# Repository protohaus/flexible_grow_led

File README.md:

# Flexible Grow LED

This project is the result of Sören Krusche's student research project.
The aim was to create a flexible LED light for growing plants with adjustable wavelengths.
It encompases the CAD files for the electronics and 3D printed components as well as the source code for the ESP8266 and the Node-RED flow.

## Node-RED Dashboard

The flow can be found in the Node-RED_Flow folder.

## PCB Design

Insert PCB image

The design files can be found in the CAD/EAGLE folder.

## 3D Printed Model

Insert 3D printed model

The design files can be found in the CAD/Fusion360 folder.

## PlatformIO Project

The source code for the ESP8266 can be found in the PlatformIO folder.

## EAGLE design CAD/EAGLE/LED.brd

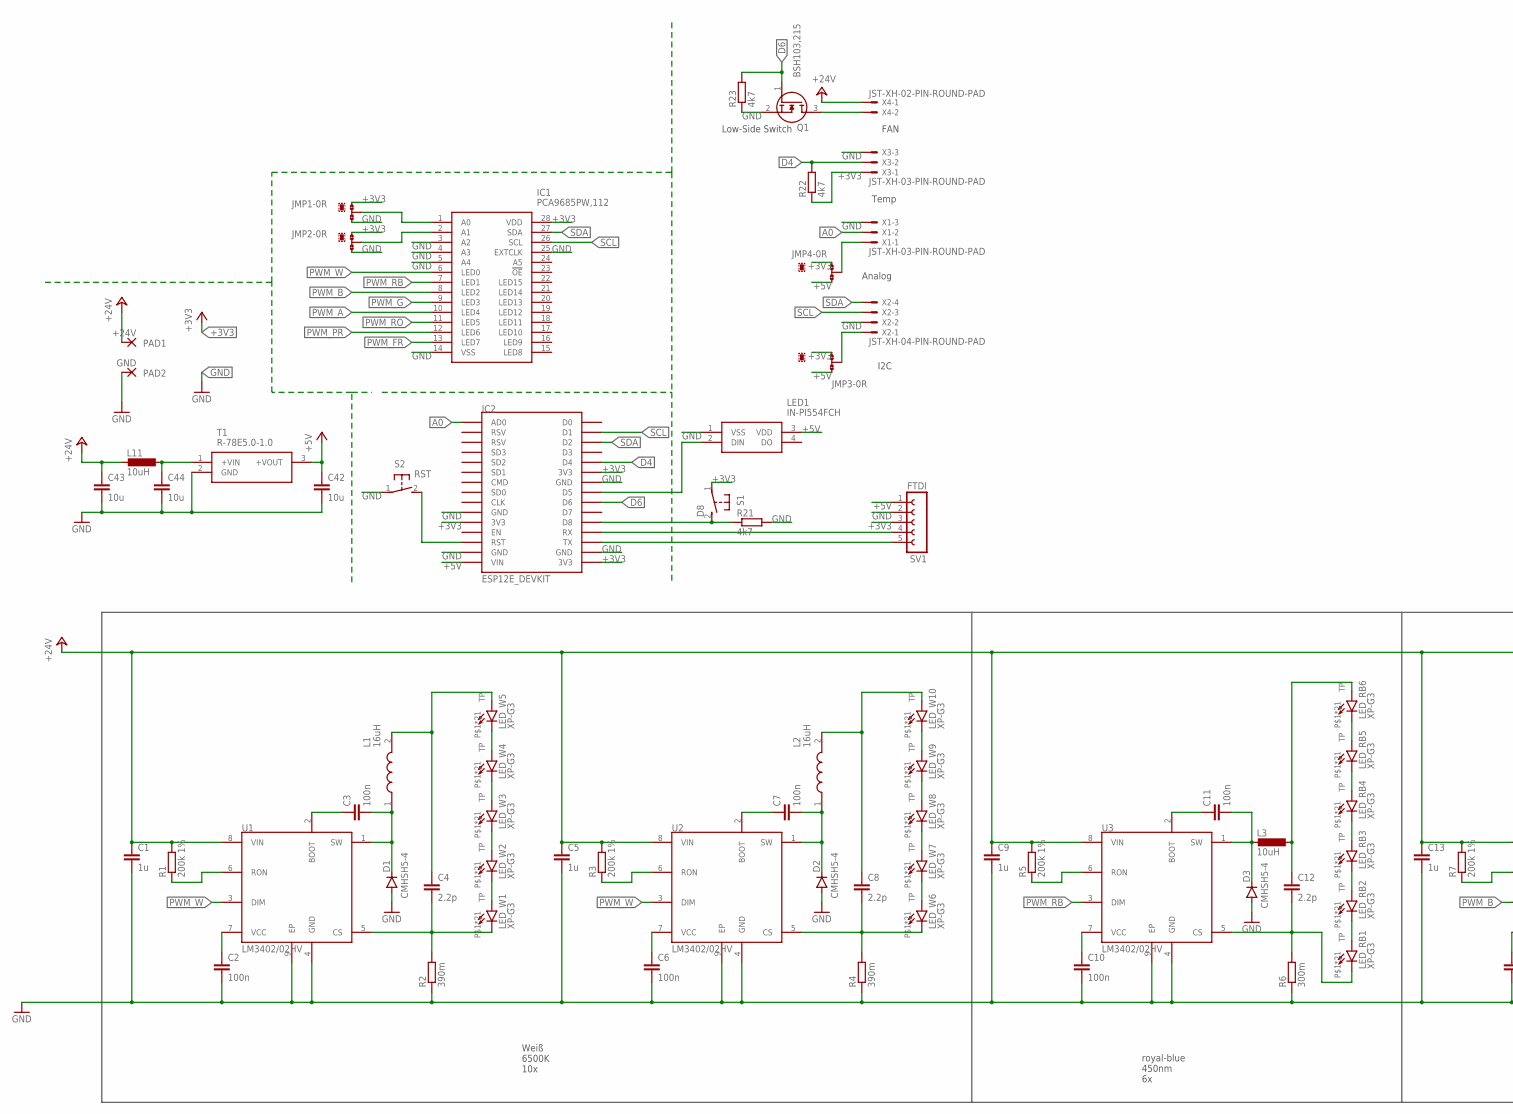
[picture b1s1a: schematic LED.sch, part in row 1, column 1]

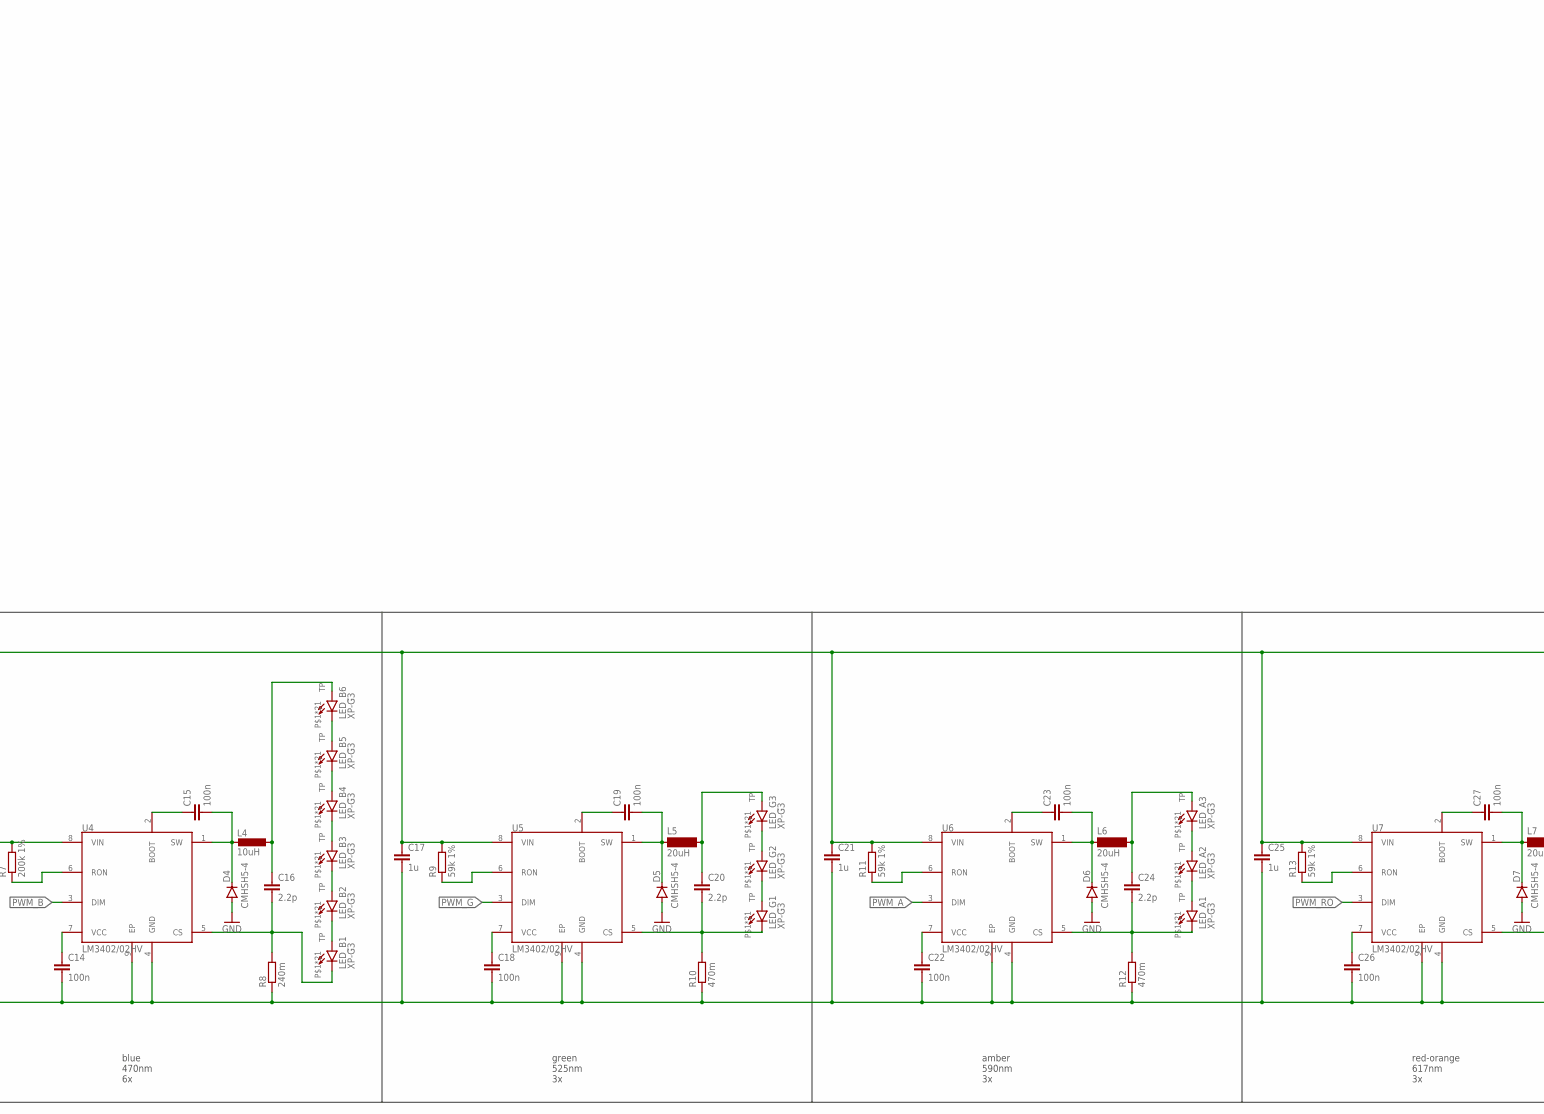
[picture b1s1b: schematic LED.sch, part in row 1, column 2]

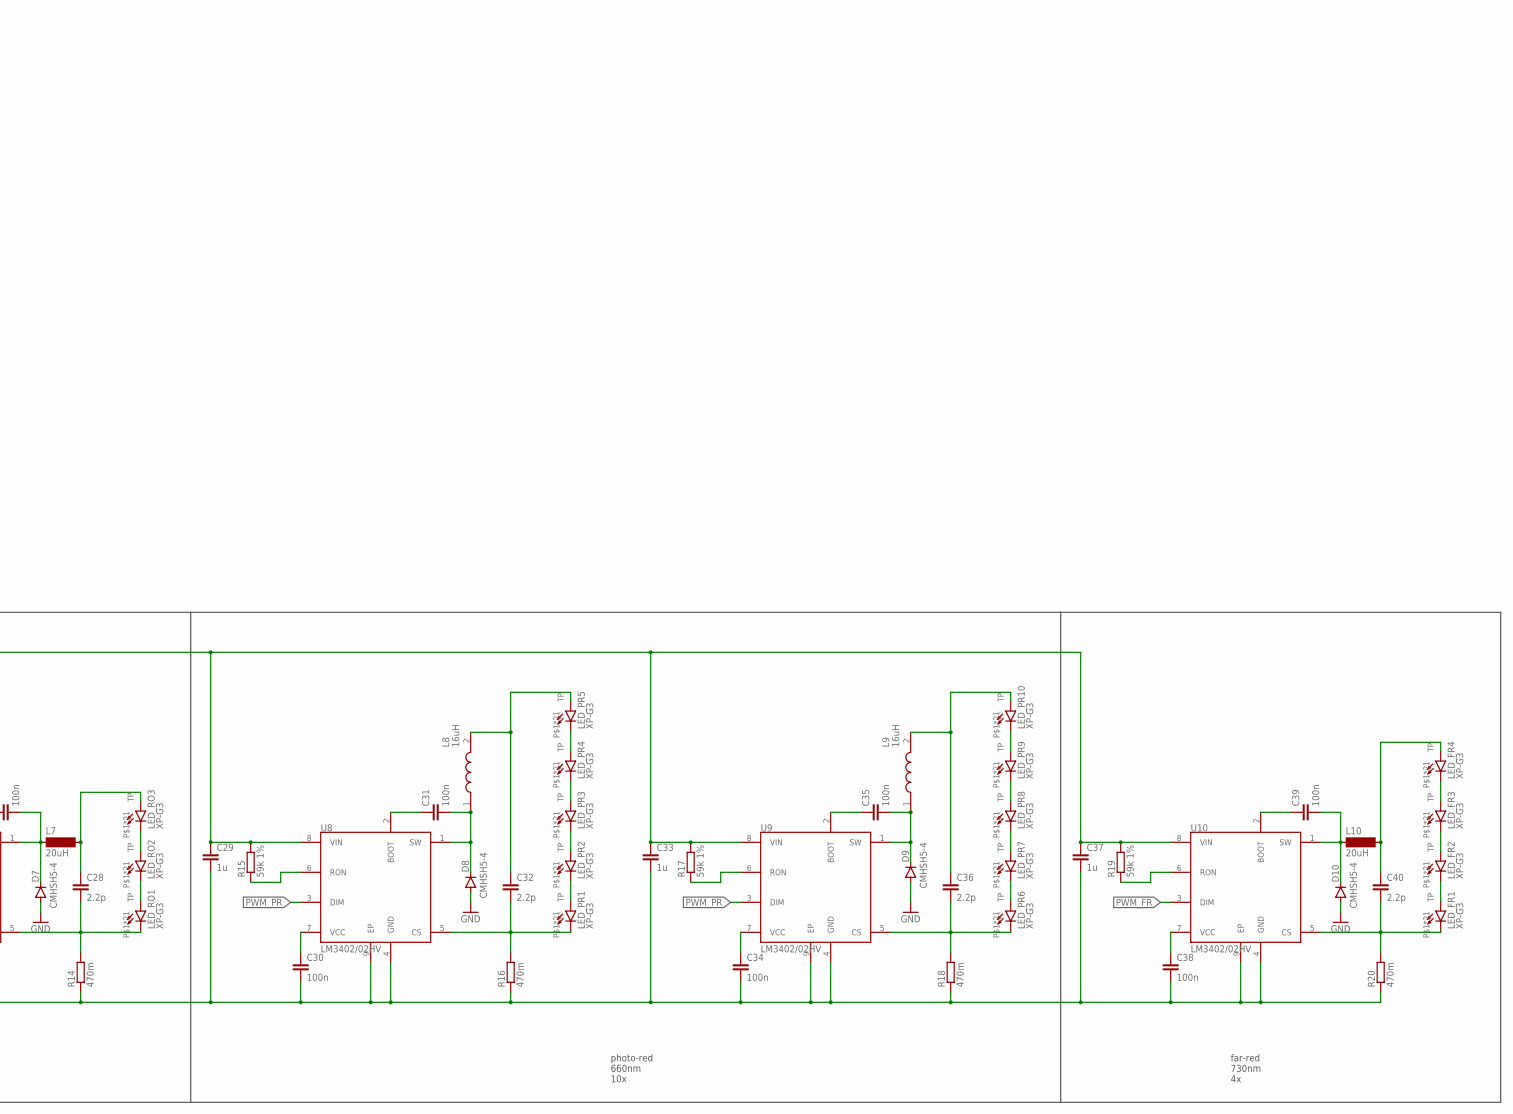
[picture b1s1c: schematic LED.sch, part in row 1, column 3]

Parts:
C1, C5, C9, C13, C17, C21, C25, C29, C33, C37: 1u; C1206
C2, C3, C6, C7, C10, C11, C14, C15, C18, C19, C22, C23, C26, C27, C30, C31, C34, C35, C38, C39: 100n; C0805
C4, C8, C12, C16, C20, C24, C28, C32, C36, C40: 2.2p; C1206
C42, C43, C44: 10u; C1210
D1, D2, D3, D4, D5, D6, D7, D8, D9, D10: CMHSH5-4; SOD123
IC1: PCA9685PW,112; SOP65P640X110-28N
IC2: ESP12E_DEVKIT
JMP1, JMP2, JMP3, JMP4: 0R-JUMPA; A0R-JMP
L1, L2, L8, L9: 16uH; INDPM101101X680N
L3, L4, L11: 10uH; L3225M
L5, L6, L7, L10: 20uH; PF0382.223NLT
LED1: IN-PI554FCH; INPI554FCH
LED_A1, LED_A2, LED_A3: XP-G3; CREE_XLAMP
LED_B1, LED_B2, LED_B3, LED_B4, LED_B5, LED_B6: XP-G3; CREE_XLAMP
LED_FR1, LED_FR2, LED_FR3, LED_FR4: XP-G3; CREE_XLAMP
LED_G1, LED_G2, LED_G3: XP-G3; CREE_XLAMP
LED_PR1, LED_PR2, LED_PR3, LED_PR4, LED_PR5, LED_PR6, LED_PR7, LED_PR8, LED_PR9, LED_PR10: XP-G3; CREE_XLAMP
LED_RB1, LED_RB2, LED_RB3, LED_RB4, LED_RB5, LED_RB6: XP-G3; CREE_XLAMP
LED_RO1, LED_RO2, LED_RO3: XP-G3; CREE_XLAMP
LED_W1, LED_W2, LED_W3, LED_W4, LED_W5, LED_W6, LED_W7, LED_W8, LED_W9, LED_W10: XP-G3; CREE_XLAMP
PAD1: +24V; 3,81/1,4
PAD2: GND; 3,81/1,4
Q1: BSH103,215; SOT95P230X110-3N
R1, R3, R5, R7: 200k 1%; R0805
R2, R4: 390m; R0805
R6: 300m; R0805
R8: 240m; R0805
R9, R11, R13, R15, R17, R19: 59k 1%; R0805
R10, R12, R14, R16, R18, R20: 470m; R0805
R21, R22, R23: 4k7; R0805
S1: D8; B3F-31XX
S2: RST; B3F-31XX
SV1: FTDI; FE05-1
T1: R-78E5.0-1.0
U1, U2, U3, U4, U5, U6, U7, U8, U9, U10: LM3402/02HV; SOIC127P600X170-9T228N
X1, X3: JST-XH-03-PIN-ROUND-PAD; JST-XH-03-PACKAGE-ROUND-PAD
X2: JST-XH-04-PIN-ROUND-PAD; JST-XH-04-PACKAGE-ROUND-PAD
X4: JST-XH-02-PIN-ROUND-PAD; JST-XH-02-PACKAGE-ROUND-PAD

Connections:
+3V3: IC1.28 (VDD), IC2.3V3@0 (3V3), IC2.3V3@1 (3V3), IC2.3V3@2 (3V3), JMP1.1, JMP2.1, JMP3.1, JMP4.1, R22.1, S1.1, SV1.3, X3.1
+5V: C42.1, IC2.VIN, JMP3.3, JMP4.3, LED1.3 (VDD), SV1.1, T1.3 (+VOUT)
+24V: C1.1, C5.1, C9.1, C13.1, C17.1, C21.1, C25.1, C29.1, C33.1, C37.1, C43.1, L11.2, PAD1.1, R1.2, R3.2, R5.2, R7.2, R9.2, R11.2, R13.2, R15.2, R17.2, R19.2, U1.8 (VIN), U2.8 (VIN), U3.8 (VIN), U4.8 (VIN), U5.8 (VIN), U6.8 (VIN), U7.8 (VIN), U8.8 (VIN), U9.8 (VIN), U10.8 (VIN), X4.1
A0: IC2.AD0, X1.2
D4: IC2.D4, R22.2, X3.2
D6: IC2.D6, Q1.1 (G), R23.2
GND: C1.2, C2.2, C5.2, C6.2, C9.2, C10.2, C13.2, C14.2, C17.2, C18.2, C21.2, C22.2, C25.2, C26.2, C29.2, C30.2, C33.2, C34.2, C37.2, C38.2, C42.2, C43.2, C44.2, D1.A, D2.A, D3.A, D4.A, D5.A, D6.A, D7.A, D8.A, D9.A, D10.A, IC1.3 (A2), IC1.4 (A3), IC1.5 (A4), IC1.14 (VSS), IC1.25 (EXTCLK), IC2.GND@0 (GND), IC2.GND@1 (GND), IC2.GND@2 (GND), IC2.GND@3 (GND), JMP1.3, JMP2.3, LED1.1 (VSS), PAD2.1, Q1.2 (S), R2.1, R4.1, R6.1, R8.1, R10.1, R12.1, R14.1, R16.1, R18.1, R20.1, R21.2, R23.1, S2.1, SV1.2, T1.2 (GND), U1.4 (GND), U1.9 (EP), U2.4 (GND), U2.9 (EP), U3.4 (GND), U3.9 (EP), U4.4 (GND), U4.9 (EP), U5.4 (GND), U5.9 (EP), U6.4 (GND), U6.9 (EP), U7.4 (GND), U7.9 (EP), U8.4 (GND), U8.9 (EP), U9.4 (GND), U9.9 (EP), U10.4 (GND), U10.9 (EP), X1.3, X2.2, X3.3
unnamed: LED_W6.A, LED_W6.A@1 (A), LED_W7.C, LED_W7.C@1 (C)
unnamed: LED_W7.A, LED_W7.A@1 (A), LED_W8.C, LED_W8.C@1 (C)
unnamed: LED_W8.A, LED_W8.A@1 (A), LED_W9.C, LED_W9.C@1 (C)
unnamed: LED_W9.A, LED_W9.A@1 (A), LED_W10.C, LED_W10.C@1 (C)
unnamed: R3.1, U2.6 (RON)
unnamed: R1.1, U1.6 (RON)
unnamed: C3.1, U1.2 (BOOT)
unnamed: C3.2, D1.C, L1.1, U1.1 (SW)
unnamed: C2.1, U1.7 (VCC)
unnamed: LED_W1.A, LED_W1.A@1 (A), LED_W2.C, LED_W2.C@1 (C)
unnamed: LED_W2.A, LED_W2.A@1 (A), LED_W3.C, LED_W3.C@1 (C)
unnamed: LED_W3.A, LED_W3.A@1 (A), LED_W4.C, LED_W4.C@1 (C)
unnamed: LED_W4.A, LED_W4.A@1 (A), LED_W5.C, LED_W5.C@1 (C)
unnamed: LED_RB5.A, LED_RB5.A@1 (A), LED_RB6.C, LED_RB6.C@1 (C)
unnamed: C4.2, LED_W1.C, LED_W1.C@1 (C), R2.2, U1.5 (CS)
unnamed: C7.1, U2.2 (BOOT)
unnamed: C7.2, D2.C, L2.1, U2.1 (SW)
unnamed: C6.1, U2.7 (VCC)
unnamed: LED_B1.A, LED_B1.A@1 (A), LED_B2.C, LED_B2.C@1 (C)
unnamed: C8.1, L2.2, LED_W10.A, LED_W10.A@1 (A)
unnamed: LED_B2.A, LED_B2.A@1 (A), LED_B3.C, LED_B3.C@1 (C)
unnamed: LED_B3.A, LED_B3.A@1 (A), LED_B4.C, LED_B4.C@1 (C)
unnamed: LED_B4.A, LED_B4.A@1 (A), LED_B5.C, LED_B5.C@1 (C)
unnamed: LED_B5.A, LED_B5.A@1 (A), LED_B6.C, LED_B6.C@1 (C)
unnamed: IC1.1 (A0), JMP1.2
unnamed: IC2.D8, R21.1, S1.2 (S)
unnamed: C8.2, LED_W6.C, LED_W6.C@1 (C), R4.2, U2.5 (CS)
unnamed: LED_RB1.A, LED_RB1.A@1 (A), LED_RB2.C, LED_RB2.C@1 (C)
unnamed: LED_RB2.A, LED_RB2.A@1 (A), LED_RB3.C, LED_RB3.C@1 (C)
unnamed: LED_RB3.A, LED_RB3.A@1 (A), LED_RB4.C, LED_RB4.C@1 (C)
unnamed: LED_RB4.A, LED_RB4.A@1 (A), LED_RB5.C, LED_RB5.C@1 (C)
unnamed: R5.1, U3.6 (RON)
unnamed: C11.1, U3.2 (BOOT)
unnamed: C11.2, D3.C, L3.2, U3.1 (SW)
unnamed: C10.1, U3.7 (VCC)
unnamed: C12.1, L3.1, LED_RB6.A, LED_RB6.A@1 (A)
unnamed: C12.2, LED_RB1.C, LED_RB1.C@1 (C), R6.2, U3.5 (CS)
unnamed: C44.1, L11.1, T1.1 (+VIN)
unnamed: IC1.2 (A1), JMP2.2
unnamed: JMP3.2, X2.1
unnamed: IC2.RST, S2.2 (S)
unnamed: JMP4.2, X1.1
unnamed: IC2.D5, LED1.2 (DIN)
unnamed: IC2.RX, SV1.4
unnamed: IC2.TX, SV1.5
unnamed: Q1.3 (D), X4.2
unnamed: R7.1, U4.6 (RON)
unnamed: C15.1, U4.2 (BOOT)
unnamed: C15.2, D4.C, L4.2, U4.1 (SW)
unnamed: C14.1, U4.7 (VCC)
unnamed: C16.1, L4.1, LED_B6.A, LED_B6.A@1 (A)
unnamed: C16.2, LED_B1.C, LED_B1.C@1 (C), R8.2, U4.5 (CS)
unnamed: LED_G1.A, LED_G1.A@1 (A), LED_G2.C, LED_G2.C@1 (C)
unnamed: LED_G2.A, LED_G2.A@1 (A), LED_G3.C, LED_G3.C@1 (C)
unnamed: R9.1, U5.6 (RON)
unnamed: C19.1, U5.2 (BOOT)
unnamed: C19.2, D5.C, L5.P0, U5.1 (SW)
unnamed: C18.1, U5.7 (VCC)
unnamed: C20.1, L5.P1, LED_G3.A, LED_G3.A@1 (A)
unnamed: C20.2, LED_G1.C, LED_G1.C@1 (C), R10.2, U5.5 (CS)
unnamed: LED_A1.A, LED_A1.A@1 (A), LED_A2.C, LED_A2.C@1 (C)
unnamed: LED_A2.A, LED_A2.A@1 (A), LED_A3.C, LED_A3.C@1 (C)
unnamed: R11.1, U6.6 (RON)
unnamed: C23.1, U6.2 (BOOT)
unnamed: C23.2, D6.C, L6.P0, U6.1 (SW)
unnamed: C22.1, U6.7 (VCC)
unnamed: C24.1, L6.P1, LED_A3.A, LED_A3.A@1 (A)
unnamed: C24.2, LED_A1.C, LED_A1.C@1 (C), R12.2, U6.5 (CS)
unnamed: LED_RO1.A, LED_RO1.A@1 (A), LED_RO2.C, LED_RO2.C@1 (C)
unnamed: LED_RO2.A, LED_RO2.A@1 (A), LED_RO3.C, LED_RO3.C@1 (C)
unnamed: R13.1, U7.6 (RON)
unnamed: C27.1, U7.2 (BOOT)
unnamed: C27.2, D7.C, L7.P0, U7.1 (SW)
unnamed: C26.1, U7.7 (VCC)
unnamed: C28.1, L7.P1, LED_RO3.A, LED_RO3.A@1 (A)
unnamed: C28.2, LED_RO1.C, LED_RO1.C@1 (C), R14.2, U7.5 (CS)
unnamed: LED_PR1.A, LED_PR1.A@1 (A), LED_PR2.C, LED_PR2.C@1 (C)
unnamed: LED_PR2.A, LED_PR2.A@1 (A), LED_PR3.C, LED_PR3.C@1 (C)
unnamed: LED_PR3.A, LED_PR3.A@1 (A), LED_PR4.C, LED_PR4.C@1 (C)
unnamed: LED_PR4.A, LED_PR4.A@1 (A), LED_PR5.C, LED_PR5.C@1 (C)
unnamed: R15.1, U8.6 (RON)
unnamed: C31.1, U8.2 (BOOT)
unnamed: C31.2, D8.C, L8.1, U8.1 (SW)
unnamed: C30.1, U8.7 (VCC)
unnamed: C32.1, L8.2, LED_PR5.A, LED_PR5.A@1 (A)
unnamed: C32.2, LED_PR1.C, LED_PR1.C@1 (C), R16.2, U8.5 (CS)
unnamed: LED_PR6.A, LED_PR6.A@1 (A), LED_PR7.C, LED_PR7.C@1 (C)
unnamed: LED_PR7.A, LED_PR7.A@1 (A), LED_PR8.C, LED_PR8.C@1 (C)
unnamed: LED_PR8.A, LED_PR8.A@1 (A), LED_PR9.C, LED_PR9.C@1 (C)
unnamed: LED_PR9.A, LED_PR9.A@1 (A), LED_PR10.C, LED_PR10.C@1 (C)
unnamed: R17.1, U9.6 (RON)
unnamed: C35.1, U9.2 (BOOT)
unnamed: C35.2, D9.C, L9.1, U9.1 (SW)
unnamed: C34.1, U9.7 (VCC)
unnamed: C36.1, L9.2, LED_PR10.A, LED_PR10.A@1 (A)
unnamed: C36.2, LED_PR6.C, LED_PR6.C@1 (C), R18.2, U9.5 (CS)
unnamed: LED_FR1.A, LED_FR1.A@1 (A), LED_FR2.C, LED_FR2.C@1 (C)
unnamed: LED_FR2.A, LED_FR2.A@1 (A), LED_FR3.C, LED_FR3.C@1 (C)
unnamed: LED_FR3.A, LED_FR3.A@1 (A), LED_FR4.C, LED_FR4.C@1 (C)
unnamed: R19.1, U10.6 (RON)
unnamed: C39.1, U10.2 (BOOT)
unnamed: C39.2, D10.C, L10.P0, U10.1 (SW)
unnamed: C38.1, U10.7 (VCC)
unnamed: C40.1, L10.P1, LED_FR4.A, LED_FR4.A@1 (A)
unnamed: C40.2, LED_FR1.C, LED_FR1.C@1 (C), R20.2, U10.5 (CS)
unnamed: C4.1, L1.2, LED_W5.A, LED_W5.A@1 (A)
PWM_A: IC1.10 (LED4), U6.3 (DIM)
PWM_B: IC1.8 (LED2), U4.3 (DIM)
PWM_FR: IC1.13 (LED7), U10.3 (DIM)
PWM_G: IC1.9 (LED3), U5.3 (DIM)
PWM_PR: IC1.12 (LED6), U8.3 (DIM), U9.3 (DIM)
PWM_RB: IC1.7 (LED1), U3.3 (DIM)
PWM_RO: IC1.11 (LED5), U7.3 (DIM)
PWM_W: IC1.6 (LED0), U1.3 (DIM), U2.3 (DIM)
SCL: IC1.26 (SCL), IC2.D1, X2.3
SDA: IC1.27 (SDA), IC2.D2, X2.4

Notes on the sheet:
Weiß 6500K 10x
royal-blue 450nm 6x
blue 470nm 6x
green 525nm 3x
amber 590nm 3x
red-orange 617nm 3x
photo-red 660nm 10x
far-red 730nm 4x
I2C
Analog
Temp
FAN
Low-Side Switch

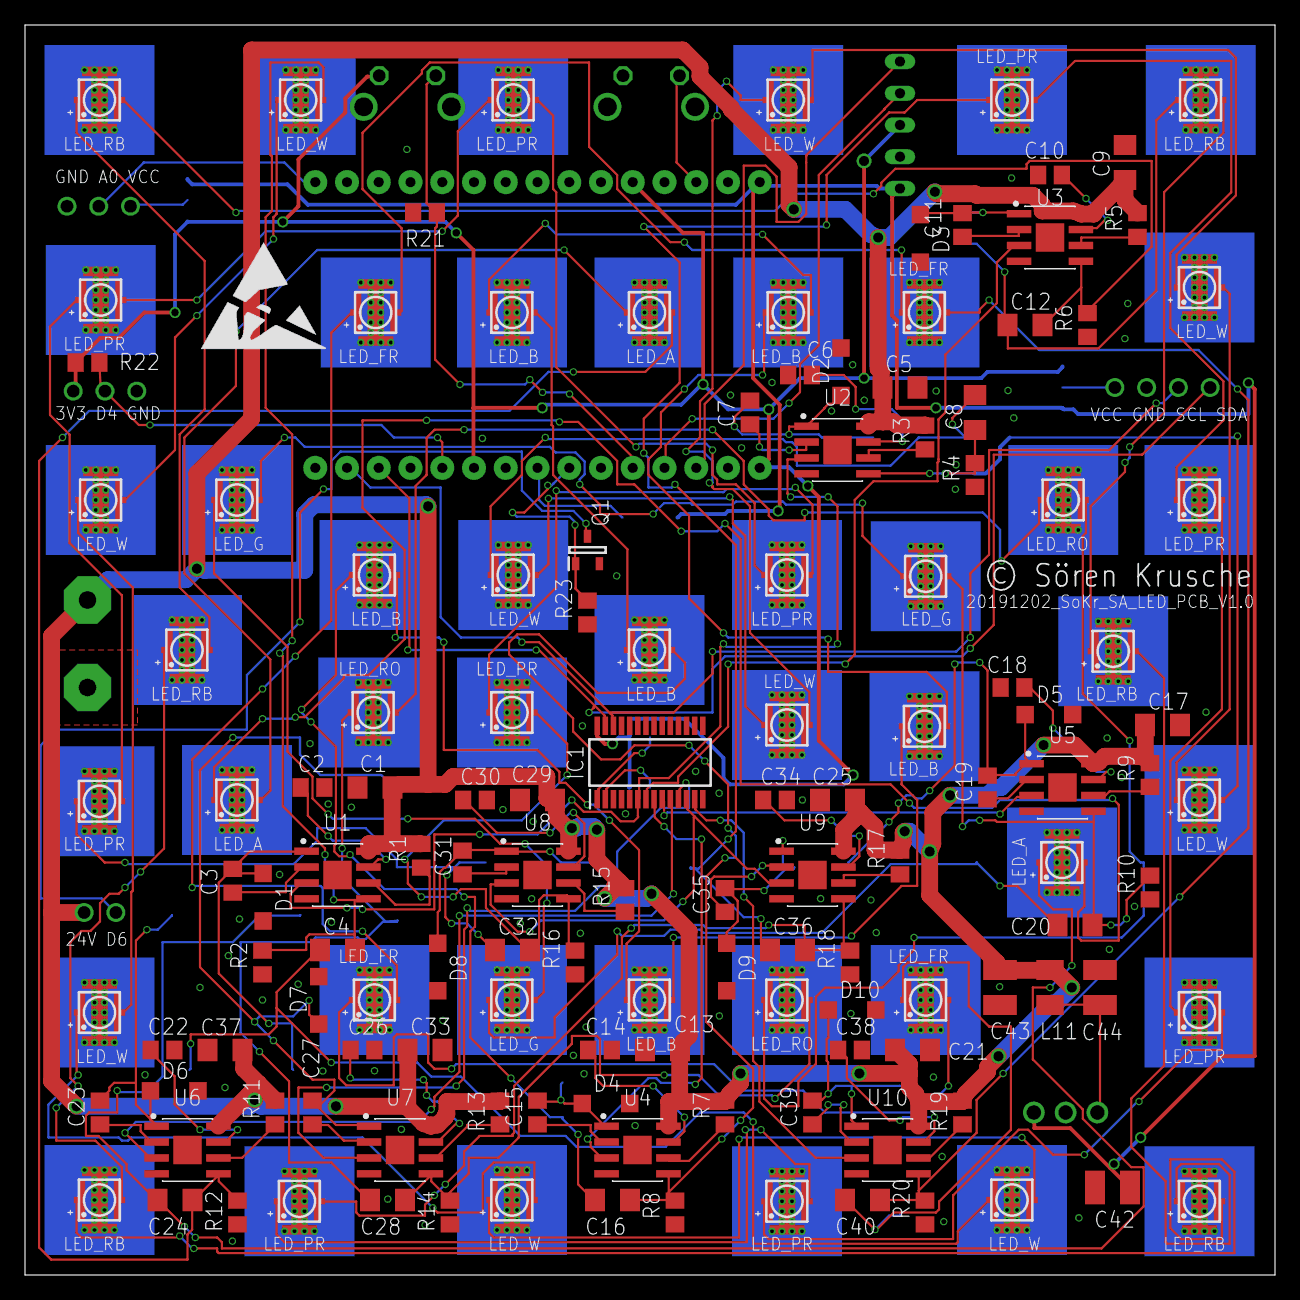
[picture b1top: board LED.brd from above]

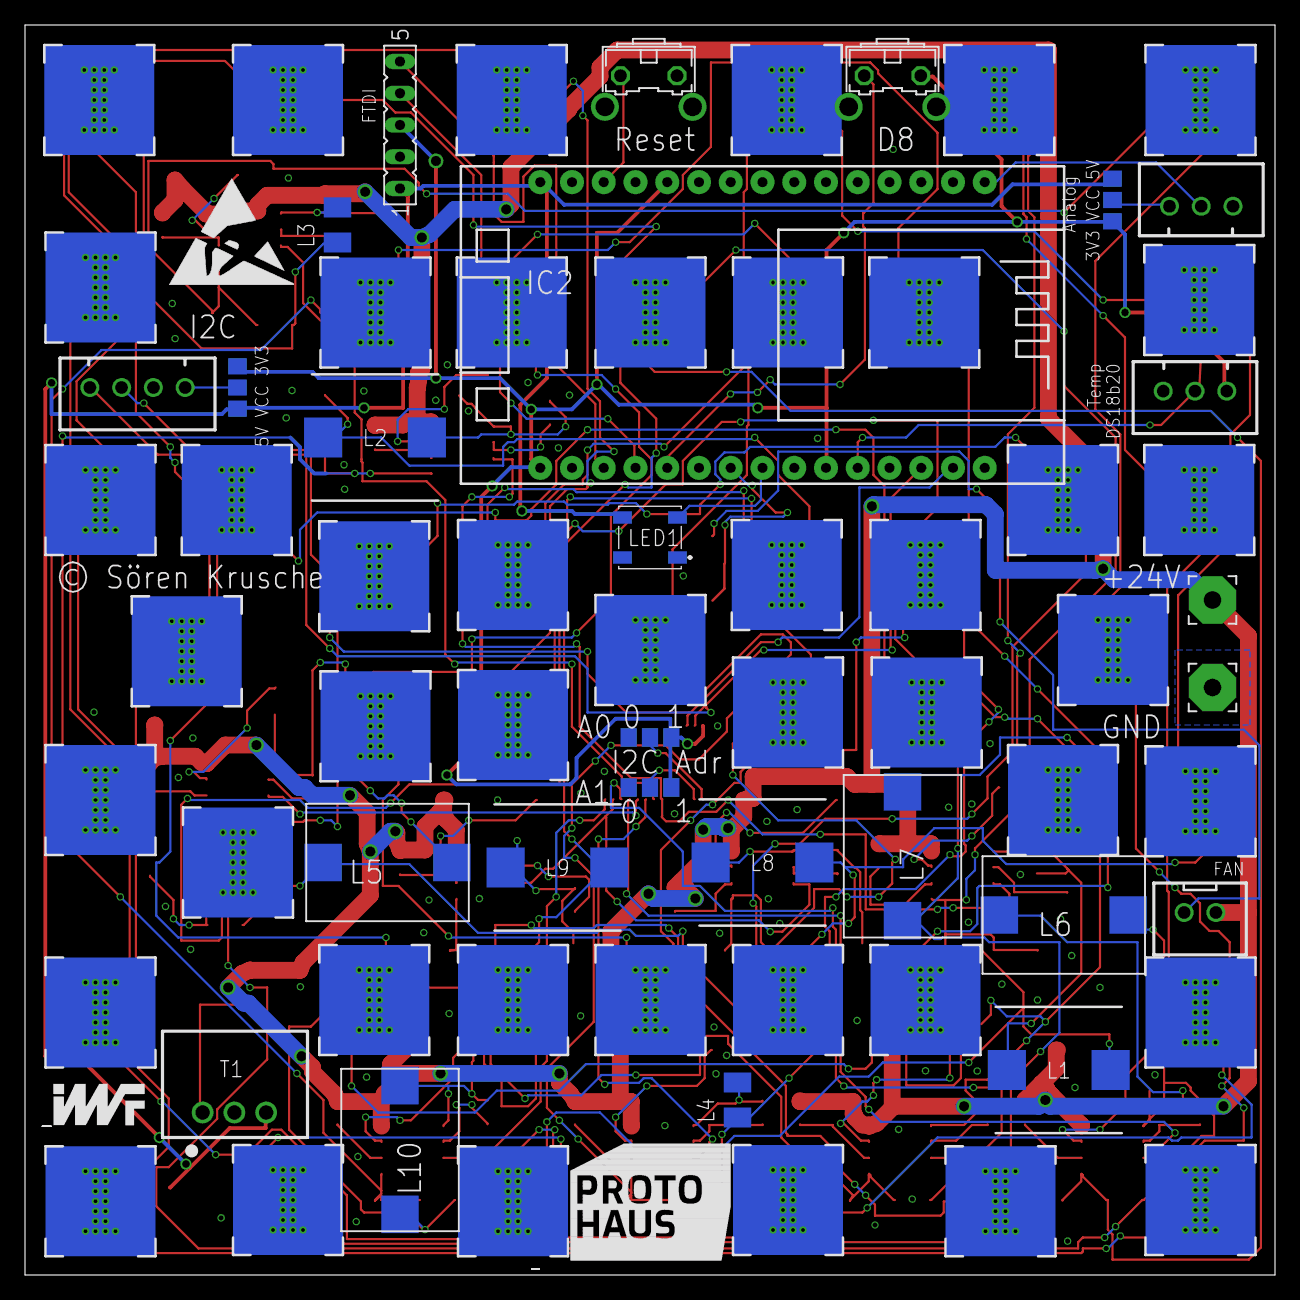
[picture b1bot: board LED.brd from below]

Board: 2 copper layers, 100.0 x 100.0 mm, 162 parts (27 on the bottom side), 123 nets.

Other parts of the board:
U$1, U$2: ESD_10.00

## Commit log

2020-09-19 Clean up documentation and organisation
    Why:
    - Simplify getting started for new users
    This change addresses the need by:
    - Change folder structure
    - Add readme file and screenshot
    - Update PlatformIO dependencies

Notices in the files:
CAD/EAGLE/LED.brd:
© Sören Krusche
